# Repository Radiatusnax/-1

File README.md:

# +1
+1 a 60 something ortho mechanical keyboard
its like an preonic but using an teensy2 with an extra row

K.R.J.E.F

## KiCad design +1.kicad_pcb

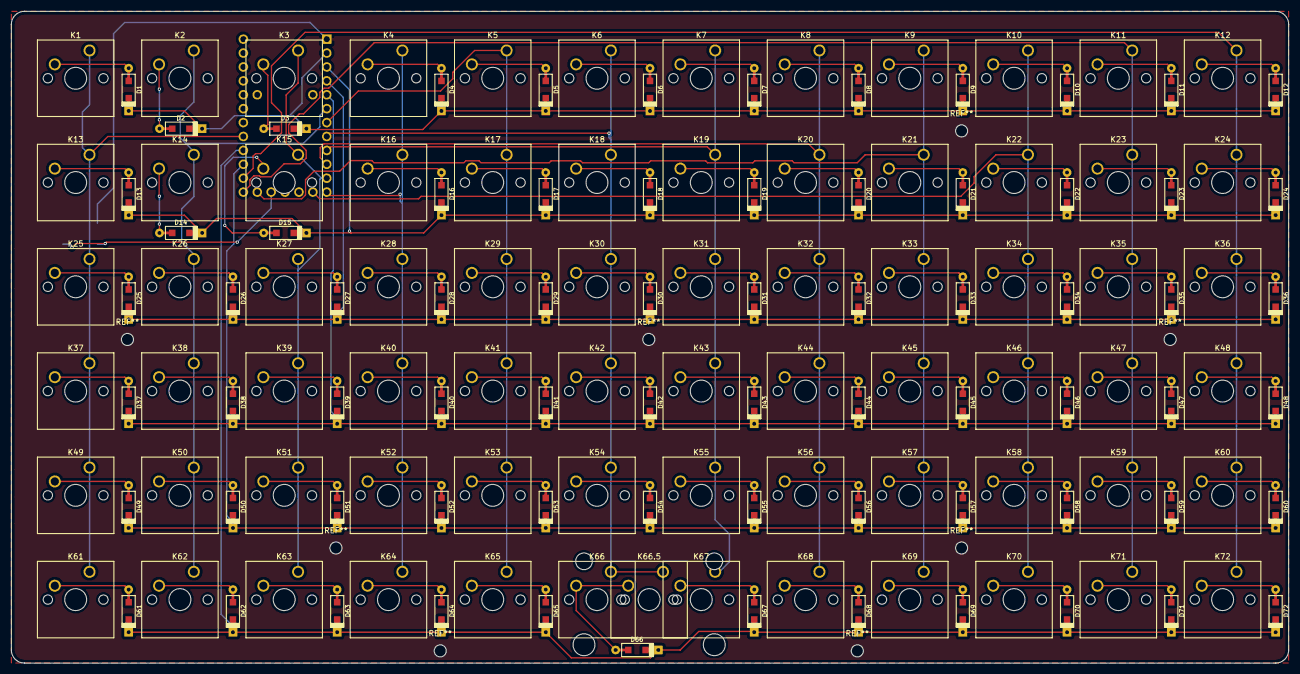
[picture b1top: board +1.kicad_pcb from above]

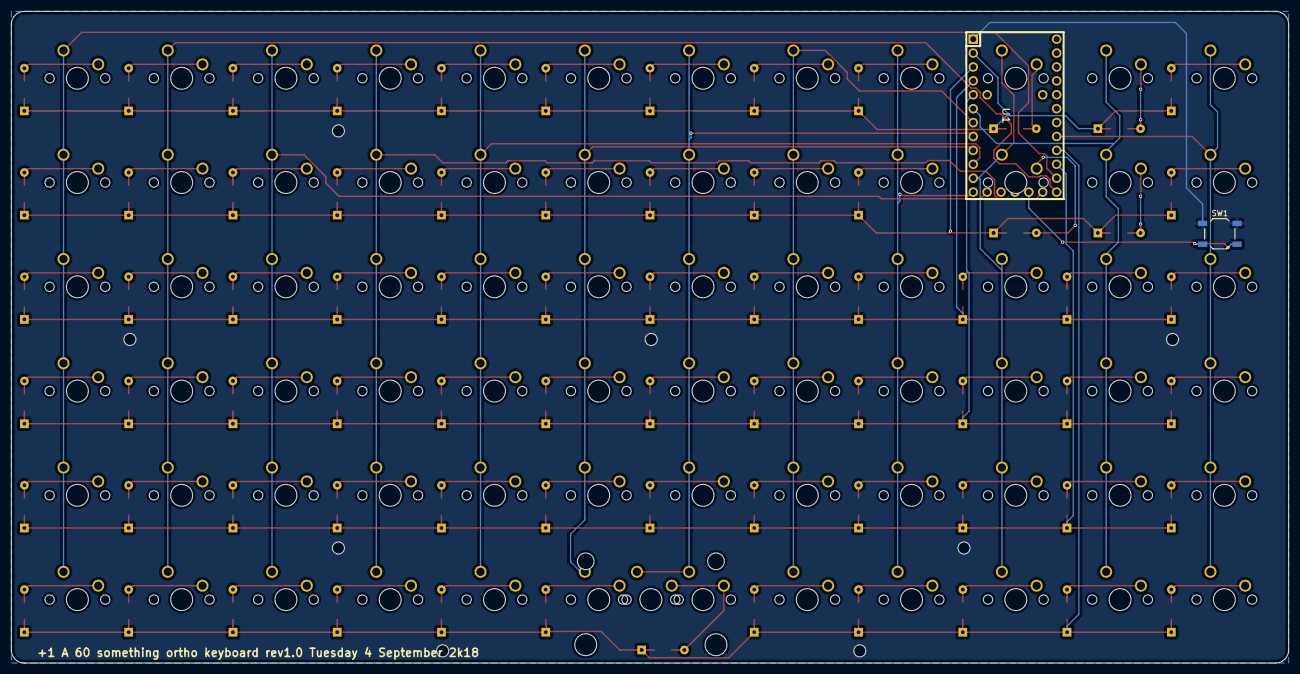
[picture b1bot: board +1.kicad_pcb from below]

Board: 2 copper layers, 233.4 x 119.1 mm, 147 parts (2 on the bottom side), 92 nets.

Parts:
D1, D2, D3, D4, D5, D6, D7, D8, D9, D10, D11, D12, D13, D14, D15, D16, D17, D18, D19, D20, D21, D22, D23, D24, D25, D26, D27, D28, D29, D30, D31, D32, D33, D34, D35, D36, D37, D38, D39, D40, D41, D42, D43, D44, D45, D46, D47, D48, D49, D50, D51, D52, D53, D54, D55, D56, D57, D58, D59, D60, D61, D62, D63, D64, D65, D66, D67, D68, D69, D70, D71, D72: D; D_SOD123_axial
K1, K2, K3, K4, K5, K6, K7, K8, K9, K10, K11, K12, K13, K14, K15, K16, K17, K18, K19, K20, K21, K22, K23, K24, K25, K26, K27, K28, K29, K30, K31, K32, K33, K34, K35, K36, K37, K38, K39, K40, K41, K42, K43, K44, K45, K46, K47, K48, K49, K50, K51, K52, K53, K54, K55, K56, K57, K58, K59, K60, K61, K62, K63, K64, K65, K66, K67, K68, K69, K70, K71, K72: KEYSW; SW_Cherry_MX1A_1.00u_PCB
K66.5: KEYSW 2.00u; SW_Cherry_MX1A_2.00u_PCB
SW1: SW_PUSH; SW_SPST_TL3342
U1: TEENSY2.0; Teensy_20

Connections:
GND: SW1.1, U1.1
unnamed: D1.2, K1.2
unnamed: D2.2, K2.2
unnamed: D3.2, K3.2
unnamed: D4.2, K4.2
unnamed: D5.2, K5.2
unnamed: D6.2, K6.2
unnamed: D7.2, K7.2
unnamed: D8.2, K8.2
unnamed: D9.2, K9.2
unnamed: D10.2, K10.2
unnamed: D11.2, K11.2
unnamed: D12.2, K12.2
unnamed: D13.2, K13.2
unnamed: D14.2, K14.2
unnamed: D15.2, K15.2
unnamed: D16.2, K16.2
unnamed: D17.2, K17.2
unnamed: D18.2, K18.2
unnamed: D19.2, K19.2
unnamed: D20.2, K20.2
unnamed: D21.2, K21.2
unnamed: D22.2, K22.2
unnamed: D23.2, K23.2
unnamed: D24.2, K24.2
unnamed: D25.2, K25.2
unnamed: D26.2, K26.2
unnamed: D27.2, K27.2
unnamed: D28.2, K28.2
unnamed: D29.2, K29.2
unnamed: D30.2, K30.2
unnamed: D31.2, K31.2
unnamed: D32.2, K32.2
unnamed: D33.2, K33.2
unnamed: D34.2, K34.2
unnamed: D35.2, K35.2
unnamed: D36.2, K36.2
unnamed: D37.2, K37.2
unnamed: D38.2, K38.2
unnamed: D39.2, K39.2
unnamed: D40.2, K40.2
unnamed: D41.2, K41.2
unnamed: D42.2, K42.2
unnamed: D43.2, K43.2
unnamed: D44.2, K44.2
unnamed: D45.2, K45.2
unnamed: D46.2, K46.2
unnamed: D47.2, K47.2
unnamed: D48.2, K48.2
unnamed: D49.2, K49.2
unnamed: D50.2, K50.2
unnamed: D51.2, K51.2
unnamed: D52.2, K52.2
unnamed: D53.2, K53.2
unnamed: D54.2, K54.2
unnamed: D55.2, K55.2
unnamed: D56.2, K56.2
unnamed: D57.2, K57.2
unnamed: D58.2, K58.2
unnamed: D59.2, K59.2
unnamed: D60.2, K60.2
unnamed: D61.2, K61.2
unnamed: D62.2, K62.2
unnamed: D63.2, K63.2
unnamed: D64.2, K64.2
unnamed: D65.2, K65.2
unnamed: D66.2, K66.2, K66.5.2
unnamed: D67.2, K67.2
unnamed: D68.2, K68.2
unnamed: D69.2, K69.2
unnamed: D70.2, K70.2
unnamed: D71.2, K71.2
unnamed: D72.2, K72.2
unnamed: SW1.2, U1.16
col0: D1.1, D2.1, D3.1, D4.1, D5.1, D6.1, D7.1, D8.1, D9.1, D10.1, D11.1, D12.1, U1.2
col1: D13.1, D14.1, D15.1, D16.1, D17.1, D18.1, D19.1, D20.1, D21.1, D22.1, D23.1, D24.1, U1.3
col2: D25.1, D26.1, D27.1, D28.1, D29.1, D30.1, D31.1, D32.1, D33.1, D34.1, D35.1, D36.1, U1.4
col3: D37.1, D38.1, D39.1, D40.1, D41.1, D42.1, D43.1, D44.1, D45.1, D46.1, D47.1, D48.1, U1.5
col4: D49.1, D50.1, D51.1, D52.1, D53.1, D54.1, D55.1, D56.1, D57.1, D58.1, D59.1, D60.1, U1.20
col5: D61.1, D62.1, D63.1, D64.1, D65.1, D66.1, D67.1, D68.1, D69.1, D70.1, D71.1, D72.1, U1.21
row0: K1.1, K13.1, K25.1, K37.1, K49.1, K61.1, U1.22
row1: K2.1, K14.1, K26.1, K38.1, K50.1, K62.1, U1.6
row2: K3.1, K15.1, K27.1, K39.1, K51.1, K63.1, U1.11
row3: K4.1, K16.1, K28.1, K40.1, K52.1, K64.1, U1.12
row4: K5.1, K17.1, K29.1, K41.1, K53.1, K65.1, U1.7
row5: K6.1, K18.1, K30.1, K42.1, K54.1, K66.1, K66.5.1, U1.8
row6: K7.1, K19.1, K31.1, K43.1, K55.1, K67.1, U1.9
row7: K8.1, K20.1, K32.1, K44.1, K56.1, K68.1, U1.10
row8: K9.1, K21.1, K33.1, K45.1, K57.1, K69.1, U1.17
row9: K10.1, K22.1, K34.1, K46.1, K58.1, K70.1, U1.13
row10: K11.1, K23.1, K35.1, K47.1, K59.1, K71.1, U1.18
row11: K12.1, K24.1, K36.1, K48.1, K60.1, K72.1, U1.19
